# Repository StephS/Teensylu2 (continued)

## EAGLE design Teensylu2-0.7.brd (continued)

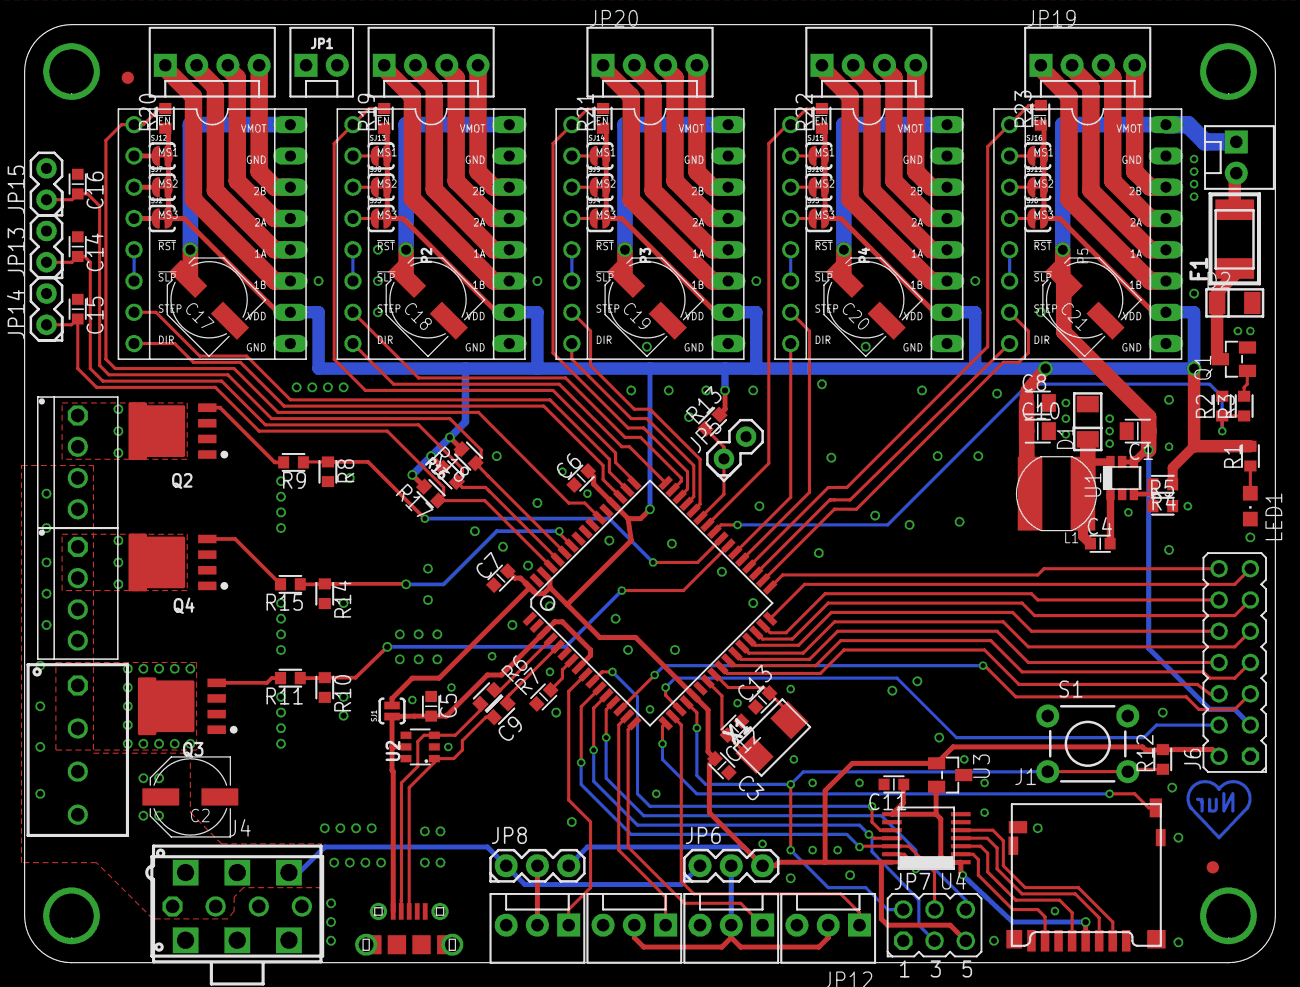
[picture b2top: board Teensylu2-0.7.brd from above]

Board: 2 copper layers, 101.6 x 76.2 mm, 113 parts (0 on the bottom side), 115 nets.

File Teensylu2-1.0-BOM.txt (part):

Partlist exported from C:/Users/stshalt/Documents/Teensylu2/Teensylu2-0.9.sch at 4/28/2015 11:14:26 AM

Qty Value                 Device                     Package             Parts                             Description                                  CURRENT DCR   DESCRIPTION                      ESR    INDUCTANCE IRMS MANUFACTURER            MANUFACTURER_PART_NUMBER      NOTES                                                                       RDS_ON   REVERSE_VOLTAGE TOLERANCE VDC VGS   VOLTAGE VOLTAGE_OUTPUT
4   0.1uF                 CAPACITOR_0603             CAPC1608X92N        C3, C5, C6, C7                                                                                                                                       Murata                  GRM188R71C104KA01D                                                                                                                 10%       16V                             
1   0.1uF                 CAPACITOR_0603             CAPC1608X92N        C4                                                                                                                                                   Samsung                 CL10B104KB8NNNC                                                                                                                    10%       50V                             
4   100                   RESISTOR_0603              RESC1608X55N        R3, R9, R11, R15                                                                                                                                                                                                                                                                                                                                          
7   100k                  RESISTOR_0603              RESC1608X55N        R12, R13, R19, R20, R21, R22, R23                                                                                                                                                                                                                                                                                                                         
6   100uF                 CPOL-USD                   PANASONIC_D         C2, C17, C18, C19, C20, C21       POLARIZED CAPACITOR, American symbol                                                                               Panasonic               EEE-FTH101XAP                                                                                                                      20%       50v                             
4   10k                   RESISTOR_0603              RESC1608X55N        R2, R8, R10, R14                                                                                                                                                                                                                                                                                                                                          
2   10pF                  CAPACITOR_0603             CAPC1608X92N        C12, C13                                                                                                                                             Samsung                 CL10C100JB8NCNC                                                                                                                    5%        50V                             
4   10uF                  CAPACITOR_0603             CAPC1608X92N        C11, C14, C15, C16                                                                                                                                   Murata                  GRM188R61C106MA73D                                                                                                                 20%       16V                             
2   10uF                  CAPACITOR_0805             CAPC2012X145AN      C8, C10                                                                                                                       0.0030                 Murata                  GRM21BR71A106KE51L                                                                                                                 10%       10v                             
1   16MHZ                 XTAL                       NDK-XTAL            X1                                                                                                                                                   NDK                     NX5032GA-16.000000MHZ-LN-CD-1                                                                                                                                                
1   1K                    RESISTOR_0603              RESC1608X55N        R1                                                                                                                                                                                                                                                                                                                                                        
1   1uF                   CAPACITOR_0603             CAPC1608X92N        C9                                                                                                                                                   Samsung                 CL10A105MO8NNNC                                                                                                                    20%       16V                             
2   22                    RESISTOR_0603              RESC1608X55N        R6, R7                                                                                                                                                                                                                                                                                                                                                    
1   2x7                   JP7Q                       JP7Q                J8                                JUMPER                                                     DIL VERTICAL PC TAIL PIN HEADER                         Harwin                  M20-9980746                                                                                                                                                                  
1   36k                   RESISTOR_0603              RESC1608X55N        R4                                                                                                                                                                                                                                                                                                              1%                                        
1   39-29-3066            39-29-3066                 39-29-3066          J6                                Mini FIT connector 6 pol Without Snap-in peg                                                                       Molex                   0039293066                                                                                                                                                                   
4   3MM-SCREW             3MM-SCREW                  PLATEDSCREW         SCREW1, SCREW2, SCREW3, SCREW4    3mm Plated Through Hole Screw                                                                                                                                                                                                                                                                                           
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
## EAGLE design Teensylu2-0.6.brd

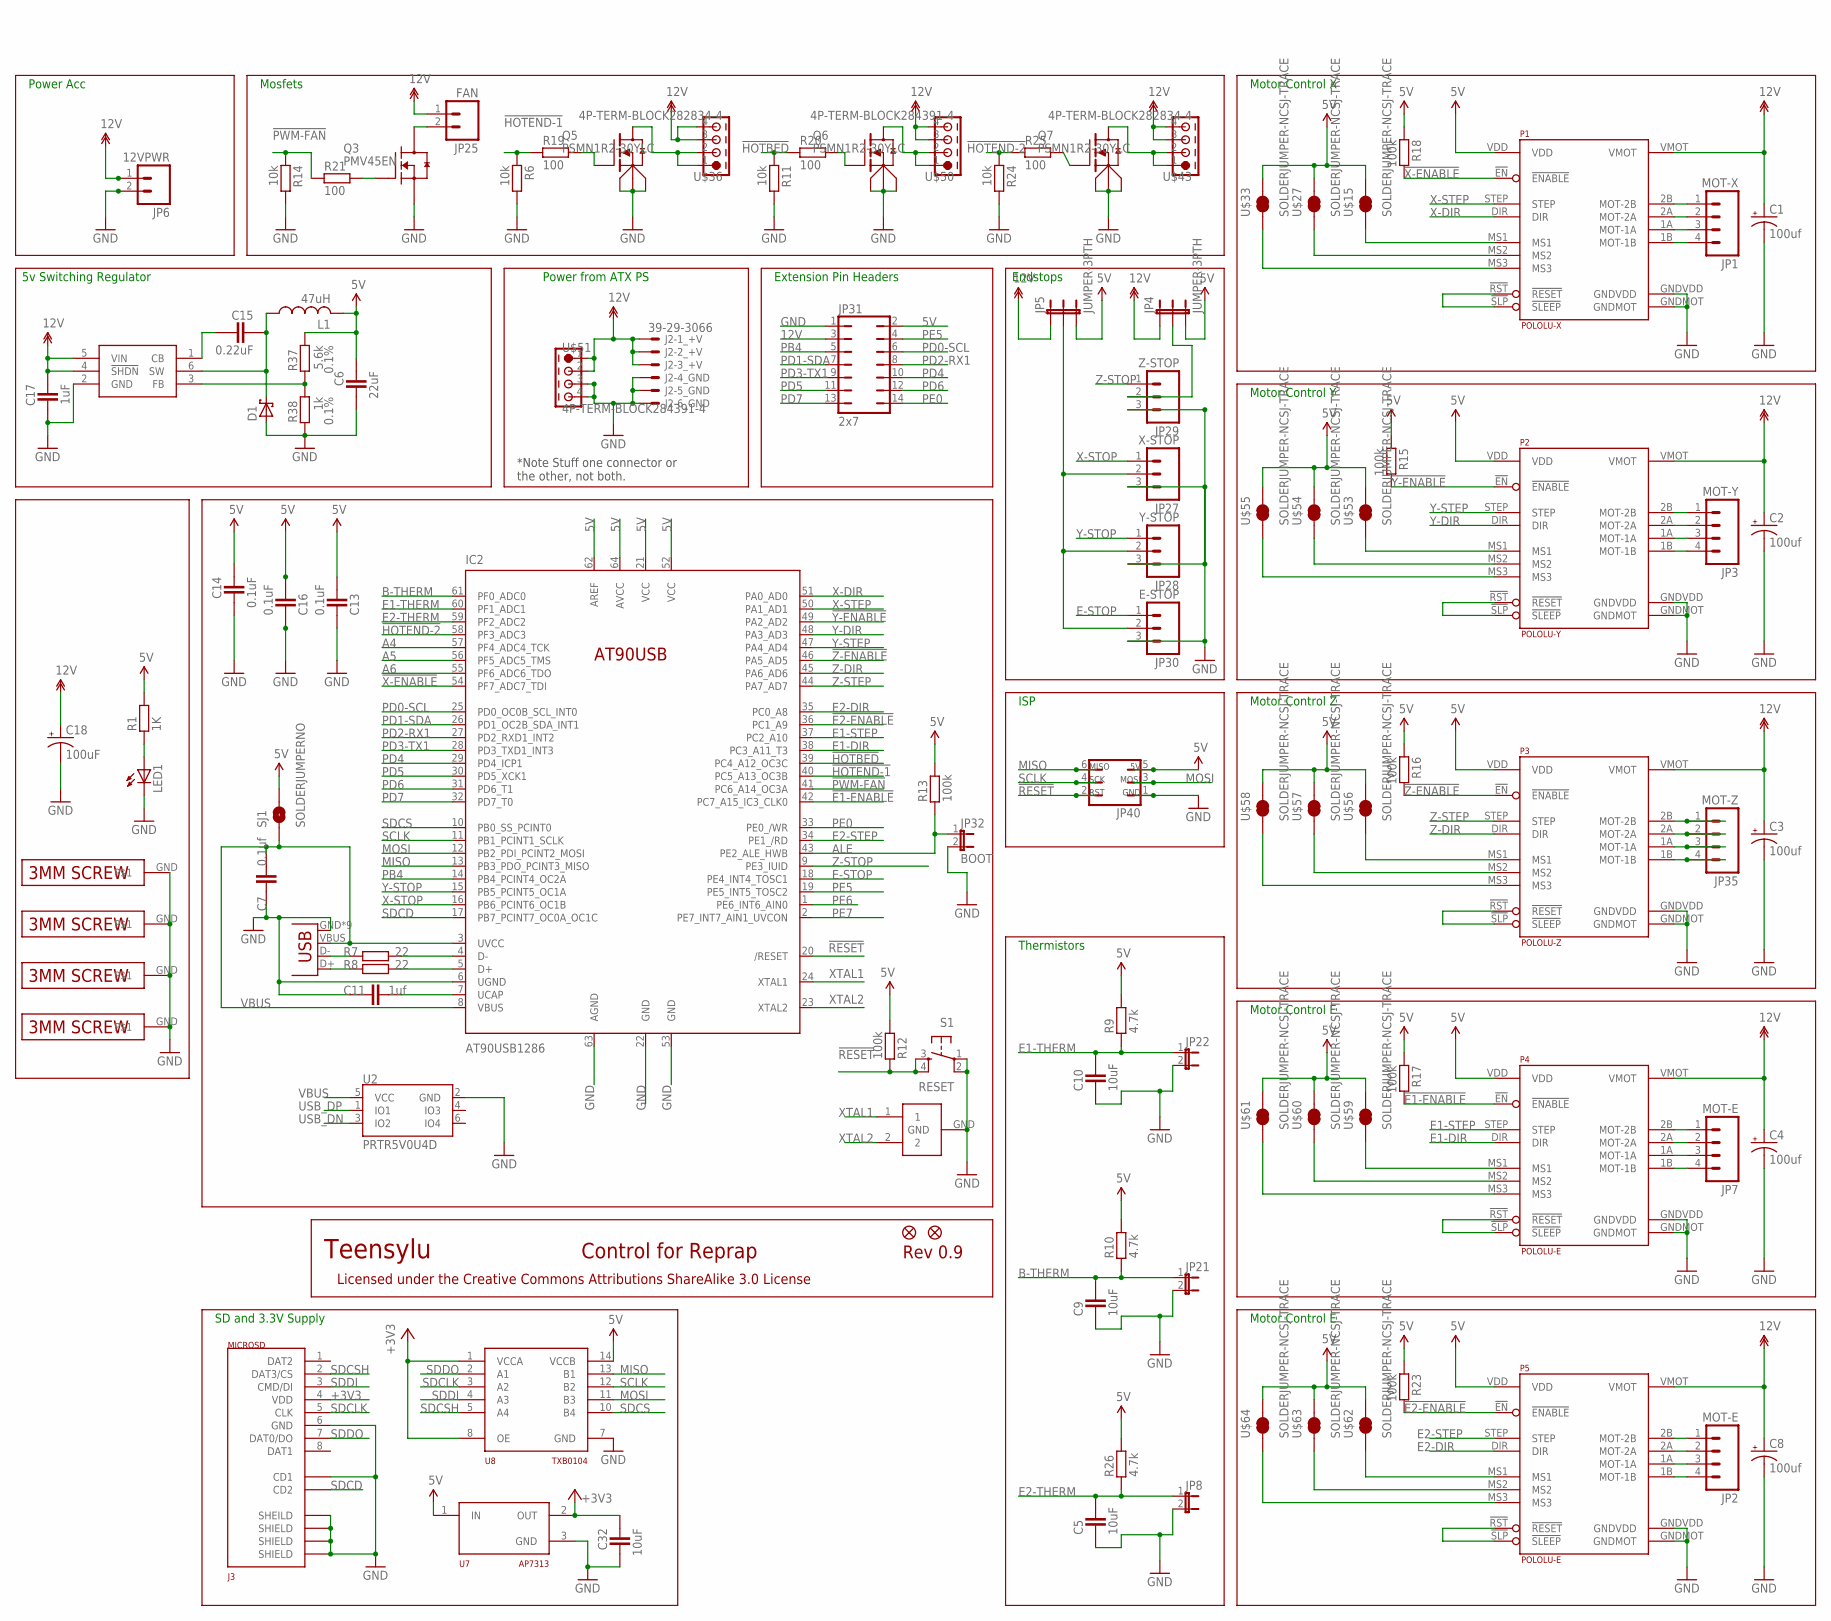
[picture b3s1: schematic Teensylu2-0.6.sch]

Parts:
C1, C2, C3, C4, C8: 100uf; CPOL-RADIAL-100UF-25V
C5, C9, C10: 10uF; CAPC1608X92N
C6: 22uF; CAPC2012X145AN
C7: 0.1uf; CAPC1608X92N
C11: 1uf; CAPC1608X92N
C13, C14, C16: 0.1uF; CAPC1608X92N
C15: 0.22uF; CAPC1608X92N
C17: 1uF; CAPC2012X145AN
C18: 100uF; PANASONIC_D
C32: 10uF; CAPC2012X145AN
D1: SCH-DIODESMA; SMA
IC2: AT90USB1286; TQFP64-2
J1: USB-MICRO-PTH; USB-MICROB-PTH
J2: 39-29-3066
J3: MICROSD; AMPHENOL-MICROSD
JP1: MOT-X; MOLEX-1X4
JP2, JP7: MOT-E; MOLEX-1X4
JP3: MOT-Y; MOLEX-1X4
JP4, JP5: JUMPER-3PTH; 1X03
JP6: 12VPWR; MOLEX-1X2
JP8, JP21, JP22: JUMPER-2PTH; 1X02
JP25: FAN; MOLEX-1X2
JP26, JP33: FIDUCIAL1X2.5; FIDUCIAL-1X2.5
JP27: X-STOP; MOLEX-1X3
JP28: Y-STOP; MOLEX-1X3
JP29: Z-STOP; MOLEX-1X3
JP30: E-STOP; MOLEX-1X3
JP31: 2x7; JP7Q
JP32: BOOT; 1X02
JP35: MOT-Z; MOLEX-1X4
JP40: PROGHEADER; ISP
L1: 47uH; SDR1006
LED1: LEDCHIPLED_0805; CHIPLED_0805
P1: POLOLU-X; POLOLU-STEPPER-PTH
P2: POLOLU-Y; POLOLU-STEPPER-PTH
P3: POLOLU-Z; POLOLU-STEPPER-PTH
P4, P5: POLOLU-E; POLOLU-STEPPER-PTH
Q3: PMV45EN; SOT95P280X135-3N
Q5, Q6, Q7: PSMN1R2-30YLC; LFPACK-POWERPAK-SO8
R1: 1K; RESC1608X55N
R6, R11, R14, R24: 10k; RESC1608X55N
R7, R8: 22; RESC1608X55N
R9, R10, R26: 4.7k; RESC1608X55N
R12, R13, R15, R16, R17, R18, R23: 100k; RESC1608X55N
R19, R20, R21, R25: 100; RESC1608X55N
R37: 5.6k; RESC1608X55N; TOLERANCE 0.1%
R38: 1k; RESC1608X55N; TOLERANCE 0.1%
S1: RESET; TACTILE-PTH
SJ1: SOLDERJUMPERNO; SJ_2S-NO
U1: LM2841; TSOT6
U2: PRTR5V0U4D; SOT23-6
U7: AP7313; SOT23C
U8: TXB0104; TSSOP14
U$15, U$27, U$33, U$53, U$54, U$55, U$56, U$57, U$58, U$59, U$60, U$61, U$62, U$63, U$64: SOLDERJUMPER-NCSJ-TRACE; SJ_2S-TRACE
U$17, U$24, U$34, U$37: 3MM-SCREW; PLATEDSCREW
U$36, U$43: 4P-TERM-BLOCK282834-4; 282834-4
U$50, U$51: 4P-TERM-BLOCK284391-4; 284391-4
XTAL: KYOCERA_PQRC_TYPE_S_RESONATOR; AVX_3.2X1.3_RESONATOR

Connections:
5V: C6.1, C13.2, C14.1, C16.2, IC2.21 (VCC), IC2.52 (VCC), IC2.62 (AREF), IC2.64 (AVCC), JP4.3, JP5.3, JP31.2, JP40.5, L1.P$2 (2), P1.VDD, P2.VDD, P3.VDD, P4.VDD, P5.VDD, R1.2, R9.2, R10.2, R12.2, R13.2, R15.1, R16.1, R17.1, R18.1, R23.1, R26.2, R37.1, SJ1.2, U7.1 (IN), U8.14 (VCCB), U$15.2, U$27.2, U$33.2, U$53.2, U$54.2, U$55.2, U$56.2, U$57.2, U$58.2, U$59.2, U$60.2, U$61.2, U$62.2, U$63.2, U$64.2
5VREG_CB: C15.2, U1.1 (CB)
5VREG_FB: R37.2, R38.1, U1.3 (FB)
5VREG_SW: C15.1, D1.C, L1.P$1 (1), U1.6 (SW)
12V: C1.1 (+), C2.1 (+), C3.1 (+), C4.1 (+), C8.1 (+), C17.1, C18.+, J2.1, J2.2, J2.3, JP4.1, JP5.1, JP6.1, JP25.1, JP31.3, P1.VMOT, P2.VMOT, P3.VMOT, P4.VMOT, P5.VMOT, U1.4 (!SHDN), U1.5 (VIN), U$36.3, U$36.4, U$43.3, U$43.4, U$50.3, U$50.4, U$51.1, U$51.2
!E1-ENABLE: IC2.42 (PC7_A15_IC3_CLK0), P4.!EN (!ENABLE), R17.2
!E2-ENABLE: IC2.36 (PC1_A9), P5.!EN (!ENABLE), R23.2
!HOTBED: IC2.39 (PC4_A12_OC3C), R11.1, R20.1
!HOTEND-1: IC2.40 (PC5_A13_OC3B), R6.1, R19.1
!HOTEND-2: IC2.58 (PF3_ADC3), R24.1, R25.1
!PWM-FAN: IC2.41 (PC6_A14_OC3A), R14.1, R21.1
!RESET: IC2.20 (/RESET), JP40.2, R12.1, S1.3, S1.4
!X-ENABLE: IC2.54 (PF7_ADC7_TDI), P1.!EN (!ENABLE), R18.2
!Y-ENABLE: IC2.49 (PA2_AD2), P2.!EN (!ENABLE), R15.2
!Z-ENABLE: IC2.46 (PA5_AD5), P3.!EN (!ENABLE), R16.2
+3V3: C32.1, J3.4 (VDD), U7.2 (OUT), U8.1 (VCCA), U8.8 (OE)
A4: IC2.57 (PF4_ADC4_TCK)
A5: IC2.56 (PF5_ADC5_TMS)
A6: IC2.55 (PF6_ADC6_TDO)
ALE: IC2.43 (PE2_ALE_HWB), JP32.1, R13.1
B-THERM: C9.2, IC2.61 (PF0_ADC0), JP21.1, R10.1
E1-DIR: IC2.38 (PC3_A11_T3), P4.DIR
E1-STEP: IC2.37 (PC2_A10), P4.STEP
E1-THERM: C10.2, IC2.60 (PF1_ADC1), JP22.1, R9.1
E2-DIR: IC2.35 (PC0_A8), P5.DIR
E2-STEP: IC2.34 (PE1_/RD), P5.STEP
E2-THERM: C5.2, IC2.59 (PF2_ADC2), JP8.1, R26.1
E-MOT-1A: JP7.3, P4.1A (MOT-1A)
E-MOT-1A1: JP2.3, P5.1A (MOT-1A)
E-MOT-1B: JP7.4, P4.1B (MOT-1B)
E-MOT-1B1: JP2.4, P5.1B (MOT-1B)
E-MOT-2A: JP7.2, P4.2A (MOT-2A)
E-MOT-2A1: JP2.2, P5.2A (MOT-2A)
E-MOT-2B: JP7.1, P4.2B (MOT-2B)
E-MOT-2B1: JP2.1, P5.2B (MOT-2B)
E-MS1: P4.MS1, U$59.1
E-MS2: P4.MS2, U$60.1
E-MS3: P4.MS3, U$61.1
E-MS4: P5.MS1, U$62.1
E-MS5: P5.MS2, U$63.1
E-MS6: P5.MS3, U$64.1
E-RESETSLEEP: P4.!RST (!RESET), P4.!SLP (!SLEEP)
E-RESETSLEEP1: P5.!RST (!RESET), P5.!SLP (!SLEEP)
E-STOP: IC2.18 (PE4_INT4_TOSC1), JP30.1
ENDSTOP+V: JP5.2, JP27.2, JP28.2, JP30.2
GND: C1.2 (-), C2.2 (-), C3.2 (-), C4.2 (-), C5.1, C6.2, C7.1, C8.2 (-), C9.1, C10.1, C11.1, C13.1, C14.2, C16.1, C17.2, C18.-, C32.2, D1.A, IC2.6 (UGND), IC2.22 (GND), IC2.53 (GND), IC2.63 (AGND), J1.GND, J1.GND1 (GND), J1.GND2 (GND), J1.GND3 (GND), J1.GND4 (GND), J1.GND5 (GND), J1.GND6 (GND), J1.GND7 (GND), J1.GND8 (GND), J2.4, J2.5, J2.6, J3.6 (GND), J3.C1 (SHEILD), J3.C2 (SHIELD), J3.C3 (SHIELD), J3.C4 (SHIELD), J3.CD1, JP6.2, JP8.2, JP21.2, JP22.2, JP27.3, JP28.3, JP29.3, JP30.3, JP31.1, JP32.2, JP40.1, LED1.C, P1.GNDMOT, P1.GNDVDD, P2.GNDMOT, P2.GNDVDD, P3.GNDMOT, P3.GNDVDD, P4.GNDMOT, P4.GNDVDD, P5.GNDMOT, P5.GNDVDD, Q3.2 (S), Q5.1 (S1), Q5.2 (S2), Q5.3 (S3), Q6.1 (S1), Q6.2 (S2), Q6.3 (S3), Q7.1 (S1), Q7.2 (S2), Q7.3 (S3), R6.2, R11.2, R14.2, R24.2, R38.2, S1.1, S1.2, U1.2 (GND), U2.2 (GND), U7.3 (GND), U8.7 (GND), U$17.GND, U$24.GND, U$34.GND, U$37.GND, U$51.3, U$51.4, XTAL.GND
HOTBED-GND: Q6.5-8 (D), U$50.1, U$50.2
HOTEND-GND: Q5.5-8 (D), U$36.1, U$36.2
HOTEND-GND1: Q7.5-8 (D), U$43.1, U$43.2
MISO: IC2.13 (PB3_PDO_PCINT3_MISO), JP40.6, U8.13 (B1)
MOSI: IC2.12 (PB2_PDI_PCINT2_MOSI), JP40.3, U8.11 (B3)
unnamed: LED1.A, R1.1
unnamed: Q6.4 (G), R20.2
unnamed: IC2.4 (D-), R7.2
unnamed: IC2.5 (D+), R8.2
unnamed: JP25.2, Q3.3 (D)
unnamed: Q3.1 (G), R21.2
unnamed: Q5.4 (G), R19.2
unnamed: Q7.4 (G), R25.2
PB4: IC2.14 (PB4_PCINT4_OC2A), JP31.5
PD0-SCL: IC2.25 (PD0_OC0B_SCL_INT0), JP31.6
PD1-SDA: IC2.26 (PD1_OC2B_SDA_INT1), JP31.7
PD2-RX1: IC2.27 (PD2_RXD1_INT2), JP31.8
PD3-TX1: IC2.28 (PD3_TXD1_INT3), JP31.9
PD4: IC2.29 (PD4_ICP1), JP31.10
PD5: IC2.30 (PD5_XCK1), JP31.11
PD6: IC2.31 (PD6_T1), JP31.12
PD7: IC2.32 (PD7_T0), JP31.13
PE0: IC2.33 (PE0_/WR), JP31.14
PE5: IC2.19 (PE5_INT5_TOSC2), JP31.4
PE6: IC2.1 (PE6_INT6_AIN0)
PE7: IC2.2 (PE7_INT7_AIN1_UVCON)
SCLK: IC2.11 (PB1_PCINT1_SCLK), JP40.4, U8.12 (B2)
SDCD: IC2.17 (PB7_PCINT7_OC0A_OC1C), J3.CD2
SDCLK: J3.5 (CLK), U8.3 (A2)
SDCS: IC2.10 (PB0_SS_PCINT0), U8.10 (B4)
SDCSH: J3.2 (DAT3/CS), U8.5 (A4)
SDDI: J3.3 (CMD/DI), U8.4 (A3)
SDDO: J3.7 (DAT0/DO), U8.2 (A1)
UCAP: C11.2, IC2.7 (UCAP)
USB_DN: J1.D-, R7.1, U2.3 (IO2)
USB_DP: J1.D+, R8.1, U2.1 (IO1)
VBUS: C7.2, IC2.3 (UVCC), IC2.8 (VBUS), J1.VBUS, SJ1.1, U2.5 (VCC)
X-DIR: IC2.51 (PA0_AD0), P1.DIR
X-MOT-1A: JP1.3, P1.1A (MOT-1A)
X-MOT-1B: JP1.4, P1.1B (MOT-1B)
X-MOT-2A: JP1.2, P1.2A (MOT-2A)
X-MOT-2B: JP1.1, P1.2B (MOT-2B)
X-MS1: P1.MS1, U$15.1
X-MS2: P1.MS2, U$27.1
X-MS3: P1.MS3, U$33.1
X-RESETSLEEP: P1.!RST (!RESET), P1.!SLP (!SLEEP)
X-STEP: IC2.50 (PA1_AD1), P1.STEP
X-STOP: IC2.16 (PB6_PCINT6_OC1B), JP27.1
XTAL1: IC2.24 (XTAL1), XTAL.1
XTAL2: IC2.23 (XTAL2), XTAL.2
Y-DIR: IC2.48 (PA3_AD3), P2.DIR
Y-MOT-1A: JP3.3, P2.1A (MOT-1A)
Y-MOT-1B: JP3.4, P2.1B (MOT-1B)
Y-MOT-2A: JP3.2, P2.2A (MOT-2A)
Y-MOT-2B: JP3.1, P2.2B (MOT-2B)
Y-MS1: P2.MS1, U$53.1
Y-MS2: P2.MS2, U$54.1
Y-MS3: P2.MS3, U$55.1
Y-RESETSLEEP: P2.!RST (!RESET), P2.!SLP (!SLEEP)
Y-STEP: IC2.47 (PA4_AD4), P2.STEP
Y-STOP: IC2.15 (PB5_PCINT5_OC1A), JP28.1
Z-DIR: IC2.45 (PA6_AD6), P3.DIR
Z-MOT-1A: JP35.3, P3.1A (MOT-1A)
Z-MOT-1B: JP35.4, P3.1B (MOT-1B)
Z-MOT-2A: JP35.2, P3.2A (MOT-2A)
Z-MOT-2B: JP35.1, P3.2B (MOT-2B)
Z-MS1: P3.MS1, U$56.1
Z-MS2: P3.MS2, U$57.1
Z-MS3: P3.MS3, U$58.1
Z-RESETSLEEP: P3.!RST (!RESET), P3.!SLP (!SLEEP)
Z-STEP: IC2.44 (PA7_AD7), P3.STEP
Z-STOP: IC2.9 (PE3_IUID), JP29.1
Z-STOP-SUPPLY: JP4.2, JP29.2

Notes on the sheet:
Motor Control X
Motor Control Y
Motor Control Z
Motor Control E
ISP
Thermistors
Endstops
Mosfets
Power Acc
Teensylu
Rev 0.9
Control for Reprap
Licensed under the Creative Commons Attributions ShareAlike 3.0 License
Extension Pin Headers
Power from ATX PS
5v Switching Regulator
SD and 3.3V Supply
*Note Stuff one connector or the other, not both.

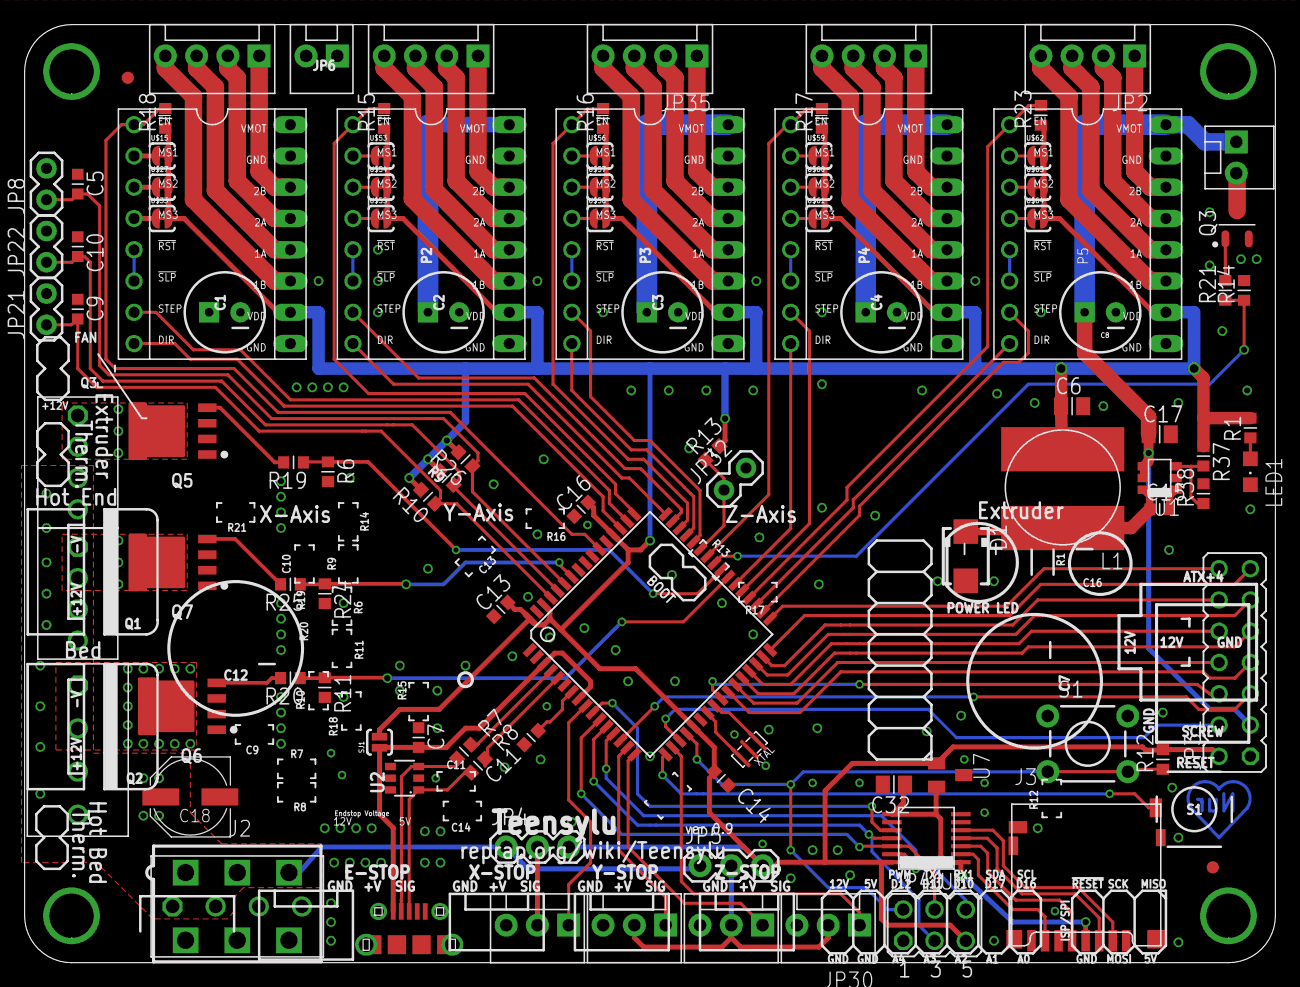
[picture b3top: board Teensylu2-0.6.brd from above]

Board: 2 copper layers, 101.6 x 76.2 mm, 108 parts (0 on the bottom side), 114 nets.

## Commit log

2015-04-22 Initial Commit
    Creating the repo
2015-04-22 Initial Teensylu2 commit, version 0.6
    This version is untested, and still needs the silkscreen updated, and a
    BOM built. DO NOT USE FOR PRODUCTION.
2015-04-23 Alpha release
    Caps have been moved over to SMD. Almost have all parts in the Teensylu
    lib. Silkscreen is still incomplete. Switched to a new regulator. Added
    attributes to all of the parts (haven't done all of the resistors yet,
    but most others should have info like the manufacturer part #, etc.)
2015-04-24 Beta Release
    This is a BETA release. The design is pending review.
    Changes:
    Added more via's to the Mosfets. Silkscreen is complete. Reset button
    changed to SMD. Moved endstop voltage selector. Capacitors are now all
    SMD. Teensylu lib should contain all of the components.
2015-04-25 Updated BOM
    Added a BOM, changed C1 to 1206 package.
2015-04-25 Adding screenshots
    Screenshots of the board and schematic.
2015-04-28 Production release
    Pin mapping is added. Had to move a lot of pins around due to limitation
    of the Teensyduino library.
2015-07-10 Fixed Z Endstop
    Collector and Emitter were swapped.
